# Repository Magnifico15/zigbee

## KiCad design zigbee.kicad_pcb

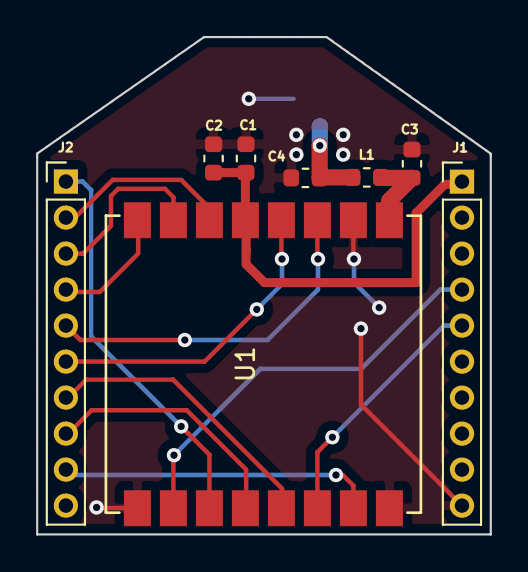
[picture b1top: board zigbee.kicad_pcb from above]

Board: 2 copper layers, 25.2 x 27.6 mm, 9 parts (1 on the bottom side), 15 nets.

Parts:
C1: 10uF; C_0603_1608Metric
C2: 0.1uF; C_0603_1608Metric
C3, C4: NP; C_0603_1608Metric
J1, J2: Conn_01x10; PinHeader_1x10_P2.00mm_Vertical
J3: u.FL; U.FL_Hirose_U.FL-R-SMT-1_Vertical
L1: OR; L_0603_1608Metric
U1: RFM95W-915S2; Ai-Thinker-Ra-01-LoRa

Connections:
+3V3: C1.1, C2.1, J1.1, U1.13
/AD2-DI02: J2.8, U1.4
/AD3-DI03: J2.7, U1.5
/AD5-DI05: J2.5, U1.11
/AD6-DI06: J2.6, U1.12
/ADI-DI0I: J2.9, U1.7
/D07-CTS: J2.2, U1.14
/D08: J1.4, U1.2
/D104: J2.1, U1.3
/ON-Sleep: J2.3, U1.15
/RESET: J1.5, U1.6
/Vref: J2.4, U1.16
GND: C1.2, C2.2, C3.2, C4.2, J1.10, J3.2, U1.1, U1.8, U1.10
unnamed: C3.1, L1.1, U1.9
unnamed: C4.1, J3.1, L1.2
